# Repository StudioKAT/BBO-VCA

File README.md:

# BBO&VCA

## 概要 / Overview

**BBO&VCA** は、Ieaskul F. Mobenthey の Denum と [crucFX Utility BBO](https://github.com/d42kn355/BoundsBounceOscillator) にインスパイアされた「バウンズ・バウンス・オシレーター（Bounds Bounce Oscillator）」です。  
この回路は、「バウンス（Bounce）」と「バウンズ（Bounds）」という、2つの概念を軸に動作します。  
ボールが2つの壁の間を行き来して跳ねている様子をイメージしてください。バウンスはボールのスピード、バウンズはその2つの壁の距離です。  
このオシレーターでは、バウンスを大きくすると周波数が上がり、バウンズを狭めると振幅が下がる代わりに周波数はさらに上がります。つまり、壁を近づけると、ボール（信号）の移動が速くなるという構造です。  
**BBO&VCA** は、バウンスとバウンズをそれぞれ独立して調整・変調でき、主出力からは常に三角波が出力されます。また、もう1つの出力からは矩形波が得られます。  
さらに、レンジスイッチにより3つの動作範囲を選択できます：
- 標準オーディオレート
- 低オーディオレート
- LFOレート

出力される三角波と矩形波は、それぞれ専用のリニアVCAを通して出力されており、外部CVやノブで音量（振幅）をコントロールできます。  
> ※ 1V/oct の標準CVピッチ制御には対応していません。

**BBO&VCA** is a "Bounds Bounce Oscillator" inspired by Ieaskul F. Mobenthey's *Denum* and the [crucFX Utility BBO](https://github.com/d42kn355/BoundsBounceOscillator).  
This circuit operates based on two key concepts: **Bounce** and **Bounds**.  
Imagine a ball bouncing back and forth between two walls. The **Bounce** represents the speed of the ball, and the **Bounds** represent the distance between the two walls.  

In this oscillator, increasing the Bounce raises the frequency. Narrowing the Bounds further increases the frequency but reduces the amplitude.  
In other words, when the walls are brought closer together, the ball (i.e., the signal) travels faster, resulting in a higher pitch.

**BBO&VCA** allows independent control and modulation of both Bounce and Bounds.  
The main output always produces a triangle wave, while the secondary output provides a square wave.  

A range switch allows you to select from three operating ranges:
- Standard audio rate  
- Low audio rate  
- LFO rate  

Both the triangle and square waves are routed through dedicated linear VCAs, allowing you to control their amplitude (volume) via knobs or external CV.

> *Note: This module does not support standard 1V/oct pitch tracking.*

## 仕様 / Spec
- Format: Eurorack
- Function: Oscillator / LFO
- Current needs: +12V: 30mA, -12V: 30mA
- Width: 8 HP
- Depth: 25mm (including power connector)

## 販売 / Sales

StudioKATオフィシャルショップで販売しています。(日本国内限定)  
 https://www.studiokat.jp/items/113562094

## ライセンス / License

この作品は [Creative Commons 表示 - 継承 4.0 国際 (CC BY-SA 4.0)](https://creativecommons.org/licenses/by-sa/4.0/deed.ja) の下でライセンスされています。  
This work is licensed under the [Creative Commons Attribution-ShareAlike 4.0 International License](https://creativecommons.org/licenses/by-sa/4.0/).

## クレジット / Credits

- Designed by : StudioKAT
- Website : https://www.studiokat.jp/
- GitHub : https://github.com/StudioKAT
- X(Twitter) : https://x.com/StudioKAT_synth
- Instagram : https://www.instagram.com/studiokat_modular/

## 更新履歴 / Changelog

- `2025-07-17` Released version 1.0

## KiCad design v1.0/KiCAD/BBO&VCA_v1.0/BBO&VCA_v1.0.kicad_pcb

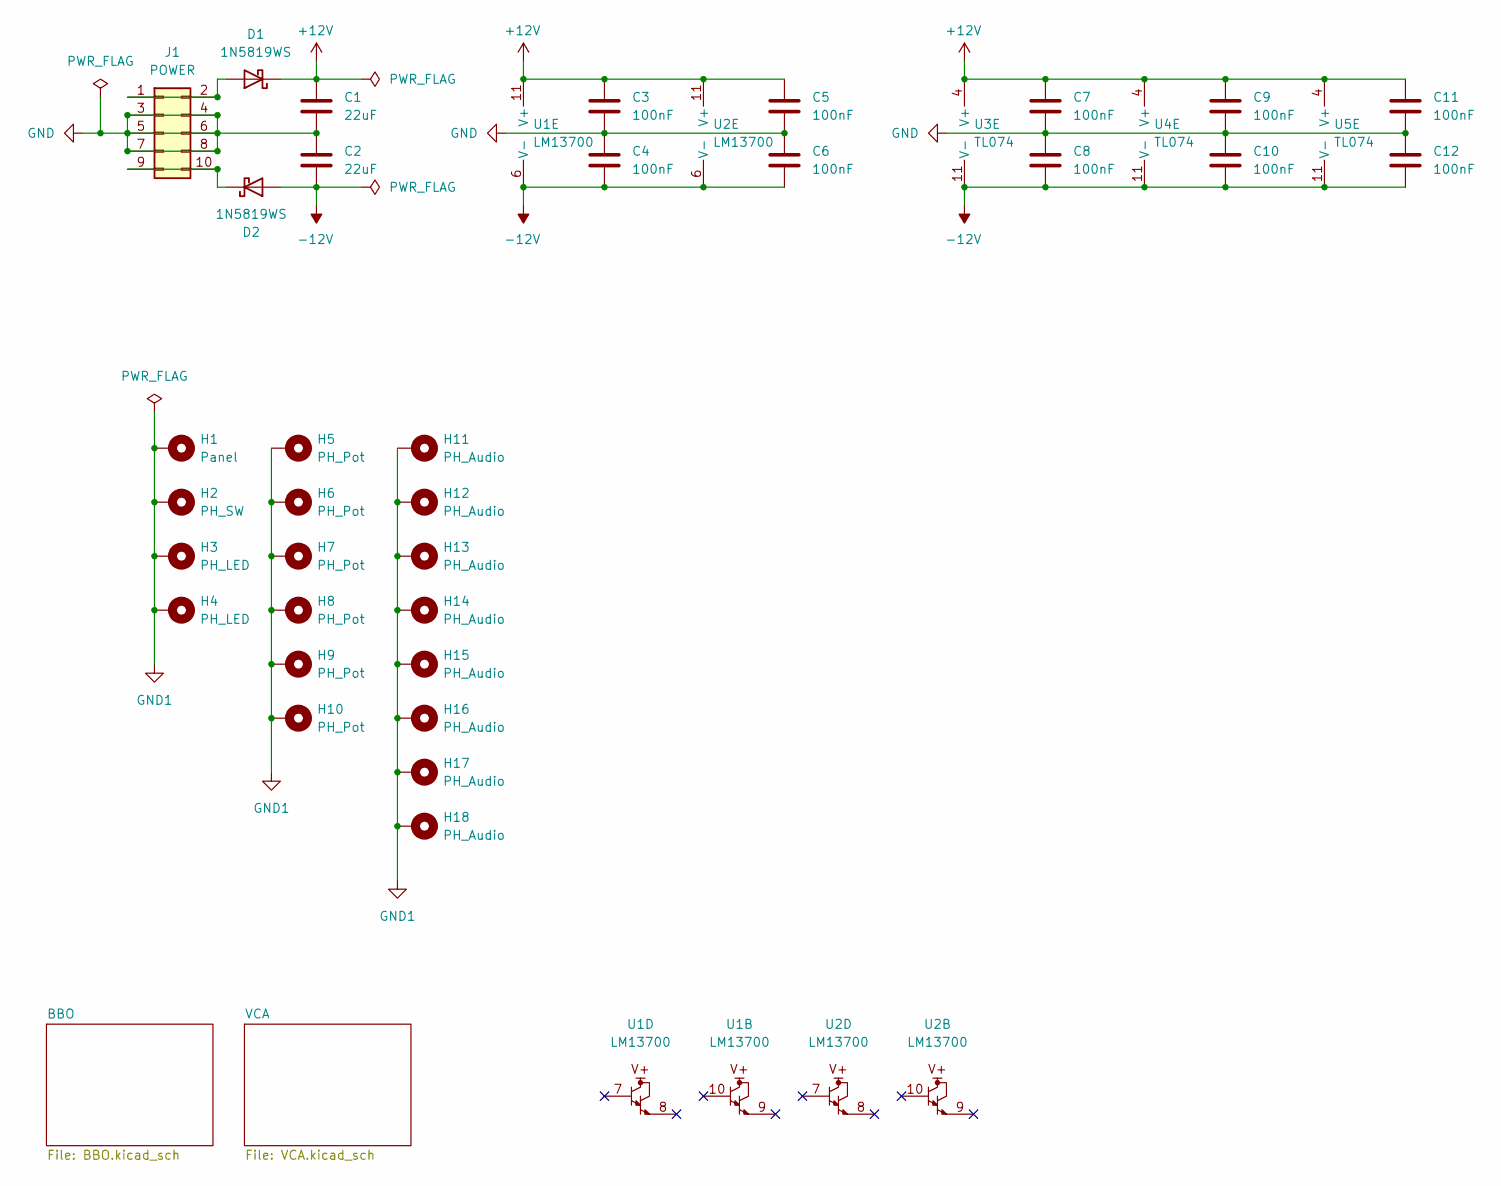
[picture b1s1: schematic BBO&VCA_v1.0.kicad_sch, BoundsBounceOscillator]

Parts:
C1, C2: 22uF; C_0805_2012Metric; LCSC C45783
C3, C4, C5, C6, C7, C8, C9, C10, C11, C12: 100nF; C_0603_1608Metric; LCSC C14663
D1, D2: 1N5819WS; D_SOD-323; LCSC C64886
H1: Panel; Panel_8HP
H2: PH_SW; PH_ToggleSwitch_5.1mm_Pad
H3, H4: PH_LED; PH_LED_3.0mm_Pad
H5, H6, H9, H10: PH_Pot; PH_RK097_15mmKnob_Pad
H7, H8: PH_Pot; PH_RK097_15mmKnob_Uni_Pad
H11, H12, H13, H14, H15, H16, H17, H18: PH_Audio; PH_AudioJack_3.5mm_Pad
J1: POWER; BoxHeader_2x05_2.54mm_Europower_2
U1, U2: LM13700; SOIC-16_3.9x9.9mm_P1.27mm; LCSC C174050
U3, U4, U5: TL074; SOIC-14_3.9x8.7mm_P1.27mm; LCSC C12594

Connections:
+12V: C1.1, C3.1, C5.1, C7.1, C9.1, C11.1, D1.1 (K), U1.11 (V+), U2.11 (V+), U3.4 (V+), U4.4 (V+), U5.4 (V+); also elsewhere on the board
-12V: C2.2, C4.2, C6.2, C8.2, C10.2, C12.2, D2.2 (A), U1.6 (V-), U2.6 (V-), U3.11 (V-), U4.11 (V-), U5.11 (V-); also elsewhere on the board
GND: C1.2, C2.1, C3.2, C4.1, C5.2, C6.1, C7.2, C8.1, C9.2, C10.1, C11.2, C12.1, J1.3, J1.4, J1.5, J1.6, J1.7, J1.8; also elsewhere on the board
GND1: H1.1, H2.1, H3.1, H4.1, H5.1, H6.1, H7.1, H8.1, H9.1, H10.1, H11.1, H12.1, H13.1, H14.1, H15.1, H16.1, H17.1, H18.1
unnamed: D1.2 (A), J1.1, J1.2
unnamed: D2.1 (K), J1.9, J1.10

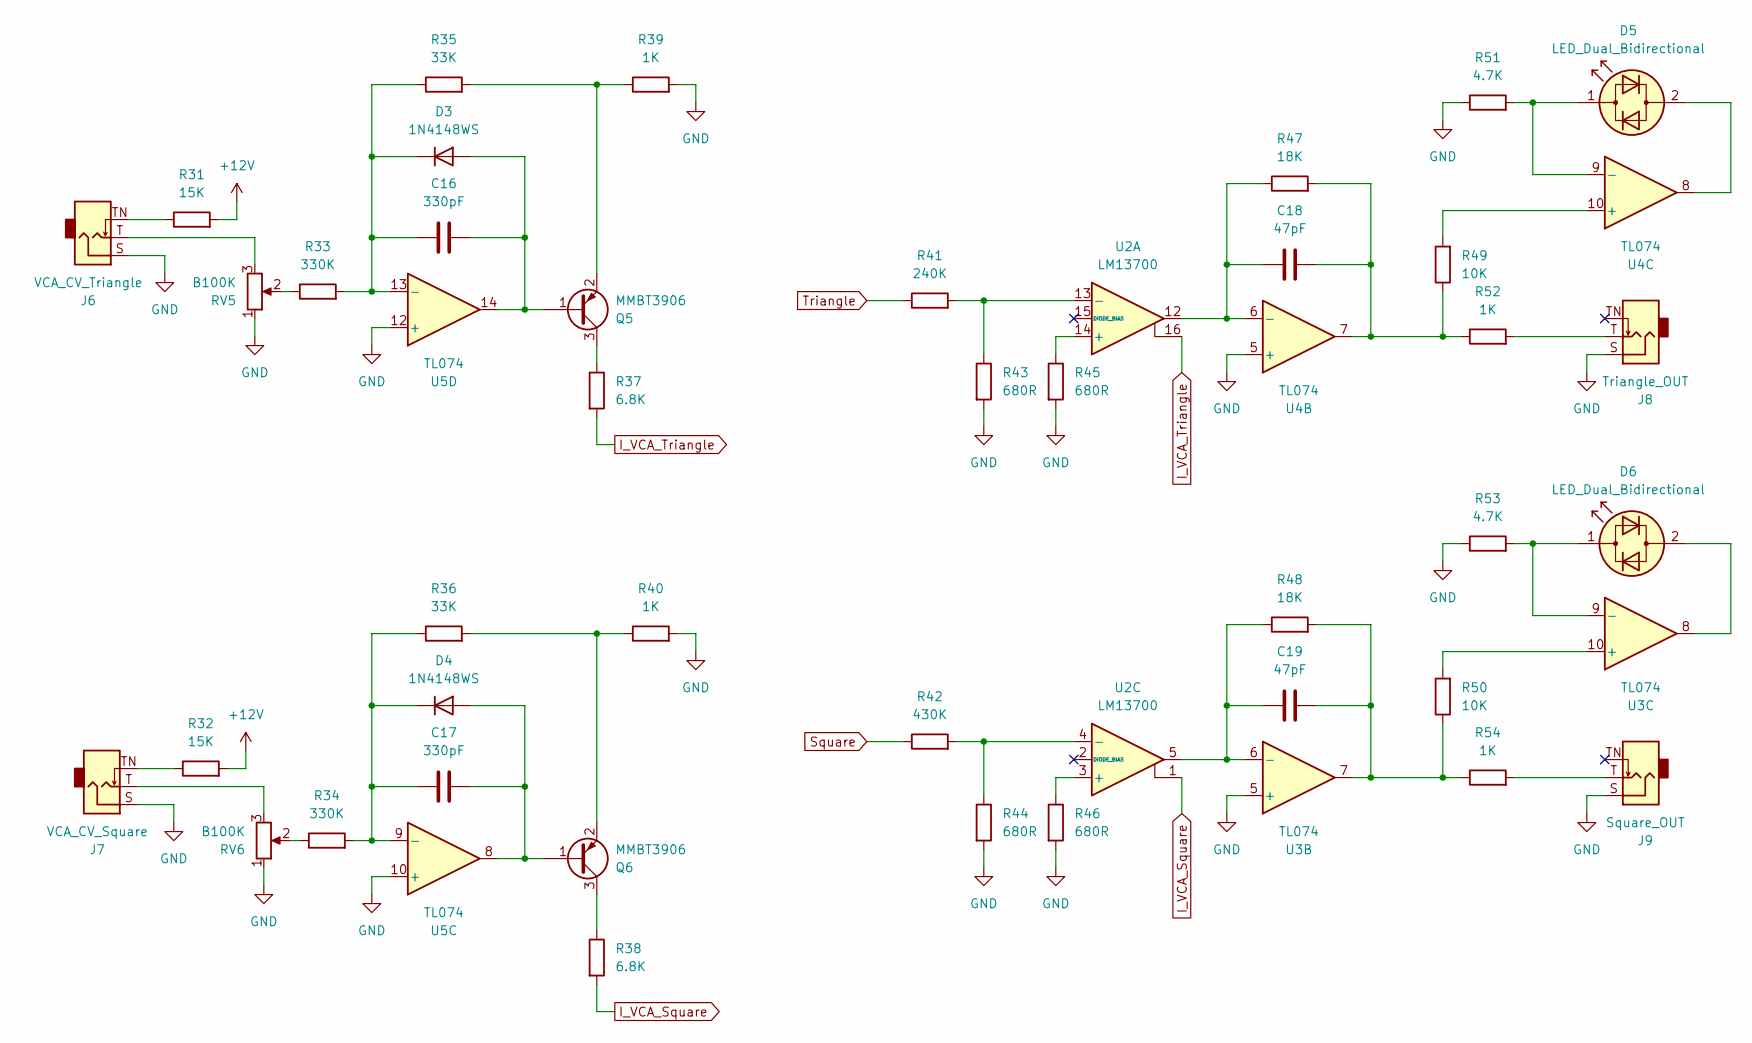
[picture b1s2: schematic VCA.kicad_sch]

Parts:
C16, C17: 330pF; C_0402_1005Metric; LCSC C13533
C18, C19: 47pF; C_0402_1005Metric; LCSC C1567
D3, D4: 1N4148WS; D_SOD-323; LCSC C2128
D5, D6: LED_Dual_Bidirectional; LED_D3.0mm
J6: VCA_CV_Triangle; AudioJack_PJ301M-12
J7: VCA_CV_Square; AudioJack_PJ301M-12
J8: Triangle_OUT; AudioJack_PJ301M-12
J9: Square_OUT; AudioJack_PJ301M-12
Q5, Q6: MMBT3906; SOT-23; LCSC C7420354
R31, R32: 15K; R_0603_1608Metric; LCSC C22809
R33, R34: 330K; R_0402_1005Metric; LCSC C25778
R35, R36: 33K; R_0402_1005Metric; LCSC C25779
R37, R38: 6.8K; R_0402_1005Metric; LCSC C25917
R39, R40, R52, R54: 1K; R_0402_1005Metric; LCSC C11702
R41: 240K; R_0603_1608Metric; LCSC C4197
R42: 430K; R_0603_1608Metric; LCSC C25969
R43, R44, R45, R46: 680R; R_0402_1005Metric; LCSC C25130
R47, R48: 18K; R_0402_1005Metric; LCSC C25762
R49, R50: 10K; R_0402_1005Metric; LCSC C25744
R51, R53: 4.7K; R_0402_1005Metric; LCSC C25900
RV5, RV6: B100K; Potentiometer_RV09
U2: LM13700; SOIC-16_3.9x9.9mm_P1.27mm; LCSC C174050
U3, U4, U5: TL074; SOIC-14_3.9x8.7mm_P1.27mm; LCSC C12594

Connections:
+12V: R31.2, R32.2; also elsewhere on the board
GND: J6.S, J7.S, J8.S, J9.S, R39.2, R40.2, R43.2, R44.2, R45.2, R46.2, R51.1, R53.1, RV5.1, RV6.1, U3.5 (+), U4.5 (+), U5.10 (+), U5.12 (+); also elsewhere on the board
I_VCA_Square: R38.2, U2.1
I_VCA_Triangle: R37.2, U2.16
unnamed: C18.2, R47.2, R49.1, R52.1, U4.7
unnamed: C19.2, R48.2, R50.1, R54.1, U3.7
unnamed: C16.2, D3.2 (A), Q5.1 (B), U5.14
unnamed: C16.1, D3.1 (K), R33.2, R35.1, U5.13 (-)
unnamed: C17.2, D4.2 (A), Q6.1 (B), U5.8
unnamed: C17.1, D4.1 (K), R34.2, R36.1, U5.9 (-)
unnamed: D5.2 (AK), U4.8
unnamed: D5.1 (KA), R51.2, U4.9 (-)
unnamed: D6.2 (AK), U3.8
unnamed: D6.1 (KA), R53.2, U3.9 (-)
unnamed: J6.T, RV5.3
unnamed: J6.TN, R31.1
unnamed: J7.T, RV6.3
unnamed: J7.TN, R32.1
unnamed: J8.T, R52.2
unnamed: J9.T, R54.2
unnamed: Q5.3 (C), R37.1
unnamed: Q5.2 (E), R35.2, R39.1
unnamed: Q6.3 (C), R38.1
unnamed: Q6.2 (E), R36.2, R40.1
unnamed: R33.1, RV5.2
unnamed: R34.1, RV6.2
unnamed: R45.1, U2.14 (+)
unnamed: R41.2, R43.1, U2.13 (-)
unnamed: R46.1, U2.3 (+)
unnamed: R42.2, R44.1, U2.4 (-)
unnamed: C19.1, R48.1, U2.5, U3.6 (-)
unnamed: R50.2, U3.10 (+)
unnamed: C18.1, R47.1, U2.12, U4.6 (-)
unnamed: R49.2, U4.10 (+)
Square: R42.1; also elsewhere on the board
Triangle: R41.1; also elsewhere on the board

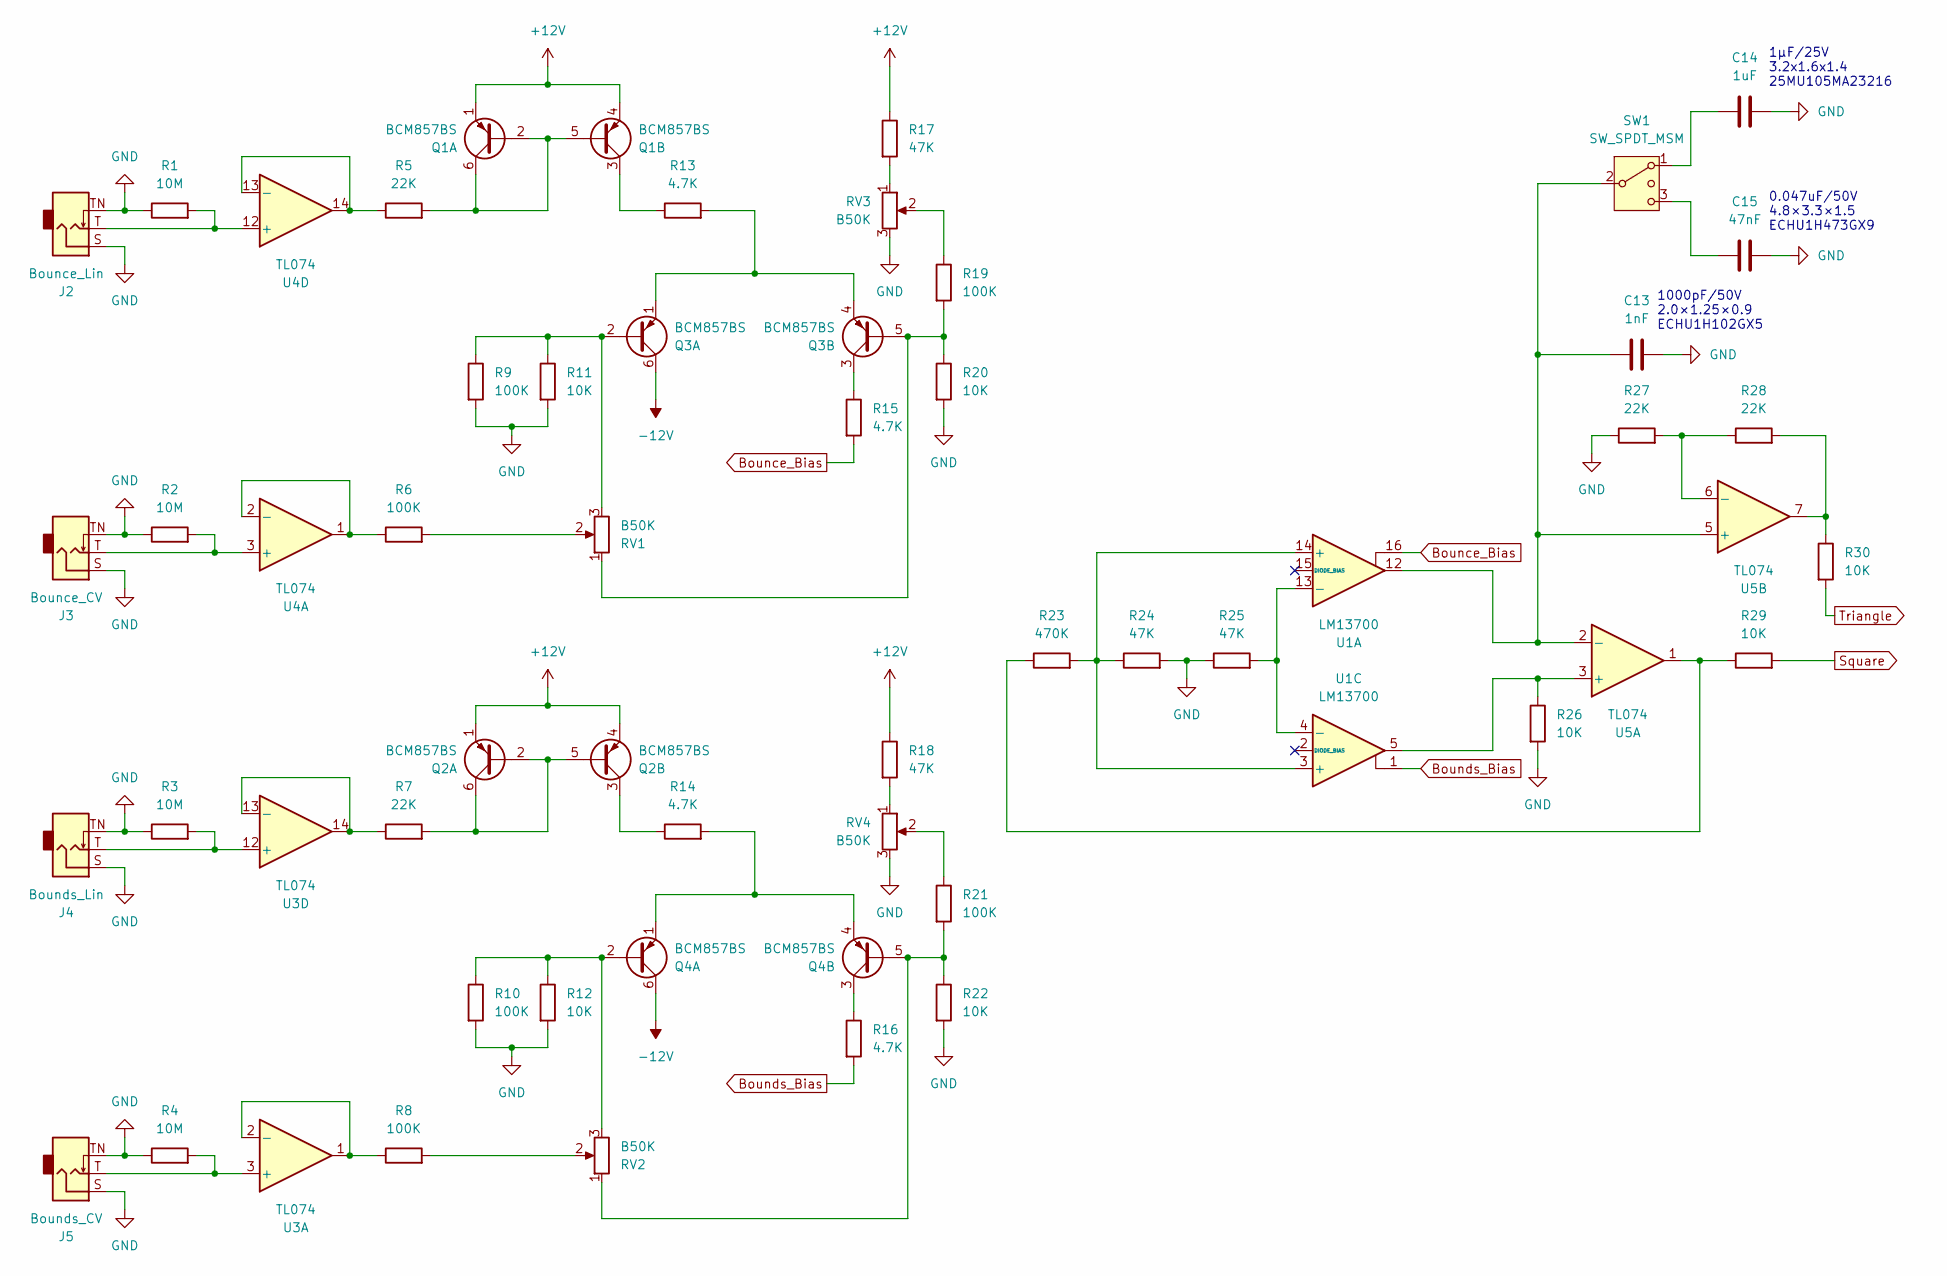
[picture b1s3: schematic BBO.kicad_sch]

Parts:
C13: 1nF; C_0805_2012Metric_Pad1.18x1.45mm_HandSolder
C14: 1uF; C_1206_3216Metric_Pad1.33x1.80mm_HandSolder
C15: 47nF; C_1913_4833Metric
J2: Bounce_Lin; AudioJack_PJ301M-12
J3: Bounce_CV; AudioJack_PJ301M-12
J4: Bounds_Lin; AudioJack_PJ301M-12
J5: Bounds_CV; AudioJack_PJ301M-12
Q1, Q2, Q3, Q4: BCM857BS; SOT-363_SC-70-6; LCSC C20426291
R1, R2, R3, R4: 10M; R_0402_1005Metric; LCSC C26082
R5, R7, R27, R28: 22K; R_0402_1005Metric; LCSC C25768
R6, R8, R9, R10, R19, R21: 100K; R_0402_1005Metric; LCSC C25741
R11, R12, R20, R22, R26, R29, R30: 10K; R_0402_1005Metric; LCSC C25744
R13, R14, R15, R16: 4.7K; R_0402_1005Metric; LCSC C25900
R17, R18, R24, R25: 47K; R_0402_1005Metric; LCSC C25792
R23: 470K; R_0402_1005Metric; LCSC C25790
RV1, RV2, RV3, RV4: B50K; Potentiometer_RV09
SW1: SW_SPDT_MSM; ToggleSwitch_2MS1-T2-B4-M2-Q-E-S
U1: LM13700; SOIC-16_3.9x9.9mm_P1.27mm; LCSC C174050
U3, U4, U5: TL074; SOIC-14_3.9x8.7mm_P1.27mm; LCSC C12594

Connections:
+12V: Q1.1 (E1), Q1.4 (E2), Q2.1 (E1), Q2.4 (E2), R17.1, R18.1; also elsewhere on the board
-12V: Q3.6 (C1), Q4.6 (C1); also elsewhere on the board
Bounce_Bias: R15.2, U1.16
Bounds_Bias: R16.2, U1.1
GND: C13.2, C14.2, C15.2, J2.S, J2.TN, J3.S, J3.TN, J4.S, J4.TN, J5.S, J5.TN, R1.1, R2.1, R3.1, R4.1, R9.2, R10.2, R11.2, R12.2, R20.2, R22.2, R24.2, R25.1, R26.2, R27.1, RV3.3, RV4.3; also elsewhere on the board
unnamed: C14.1, SW1.1
unnamed: Q1.2 (B1), Q1.5 (B2), Q1.6 (C1), R5.2
unnamed: Q1.3 (C2), R13.1
unnamed: Q2.2 (B1), Q2.5 (B2), Q2.6 (C1), R7.2
unnamed: Q2.3 (C2), R14.1
unnamed: Q3.2 (B1), R9.1, R11.1, RV1.3
unnamed: Q3.1 (E1), Q3.4 (E2), R13.2
unnamed: Q3.5 (B2), R19.2, R20.1, RV1.1
unnamed: Q3.3 (C2), R15.1
unnamed: Q4.2 (B1), R10.1, R12.1, RV2.3
unnamed: Q4.1 (E1), Q4.4 (E2), R14.2
unnamed: Q4.5 (B2), R21.2, R22.1, RV2.1
unnamed: Q4.3 (C2), R16.1
unnamed: R6.2, RV1.2
unnamed: R8.2, RV2.2
unnamed: R17.2, RV3.1
unnamed: R18.2, RV4.1
unnamed: R19.1, RV3.2
unnamed: R21.1, RV4.2
unnamed: R23.1, R29.1, U5.1
unnamed: R28.2, R30.1, U5.7
unnamed: C13.1, SW1.2 (3), U1.12, U5.2 (-), U5.5 (+)
unnamed: C15.1, SW1.3 (4)
unnamed: R23.2, R24.1, U1.3 (+), U1.14 (+)
unnamed: R25.2, U1.4 (-), U1.13 (-)
unnamed: J5.T, R4.2, U3.3 (+)
unnamed: R8.1, U3.1, U3.2 (-)
unnamed: J4.T, R3.2, U3.12 (+)
unnamed: R7.1, U3.13 (-), U3.14
unnamed: J3.T, R2.2, U4.3 (+)
unnamed: R6.1, U4.1, U4.2 (-)
unnamed: J2.T, R1.2, U4.12 (+)
unnamed: R5.1, U4.13 (-), U4.14
unnamed: R26.1, U1.5, U5.3 (+)
unnamed: R27.2, R28.1, U5.6 (-)
Square: R29.2; also elsewhere on the board
Triangle: R30.2; also elsewhere on the board

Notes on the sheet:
0.047uF/50V 4.8×3.3×1.5 ECHU1H473GX9
1μF/25V 3.2x1.6x1.4 25MU105MA23216
1000pF/50V 2.0×1.25×0.9 ECHU1H102GX5

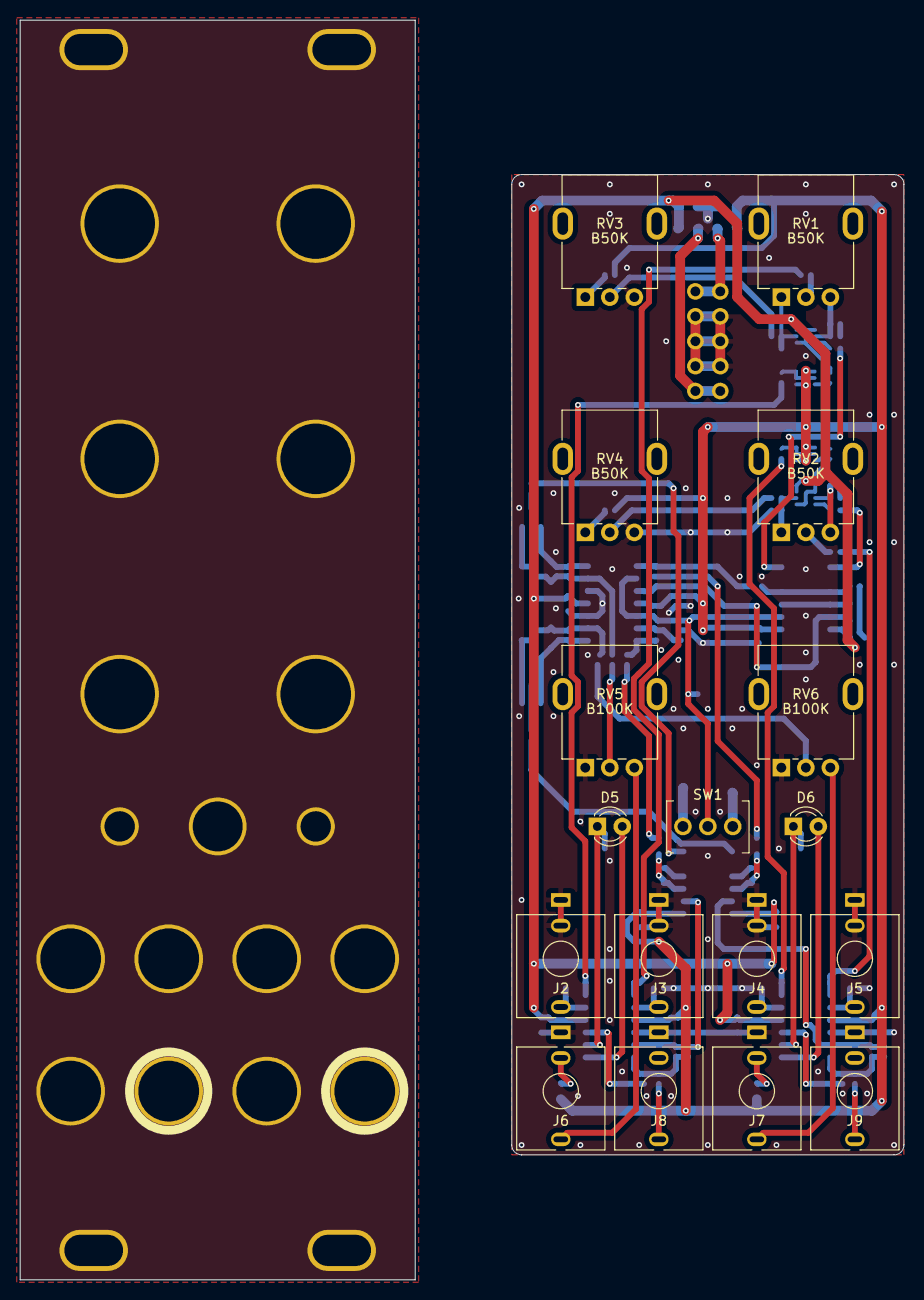
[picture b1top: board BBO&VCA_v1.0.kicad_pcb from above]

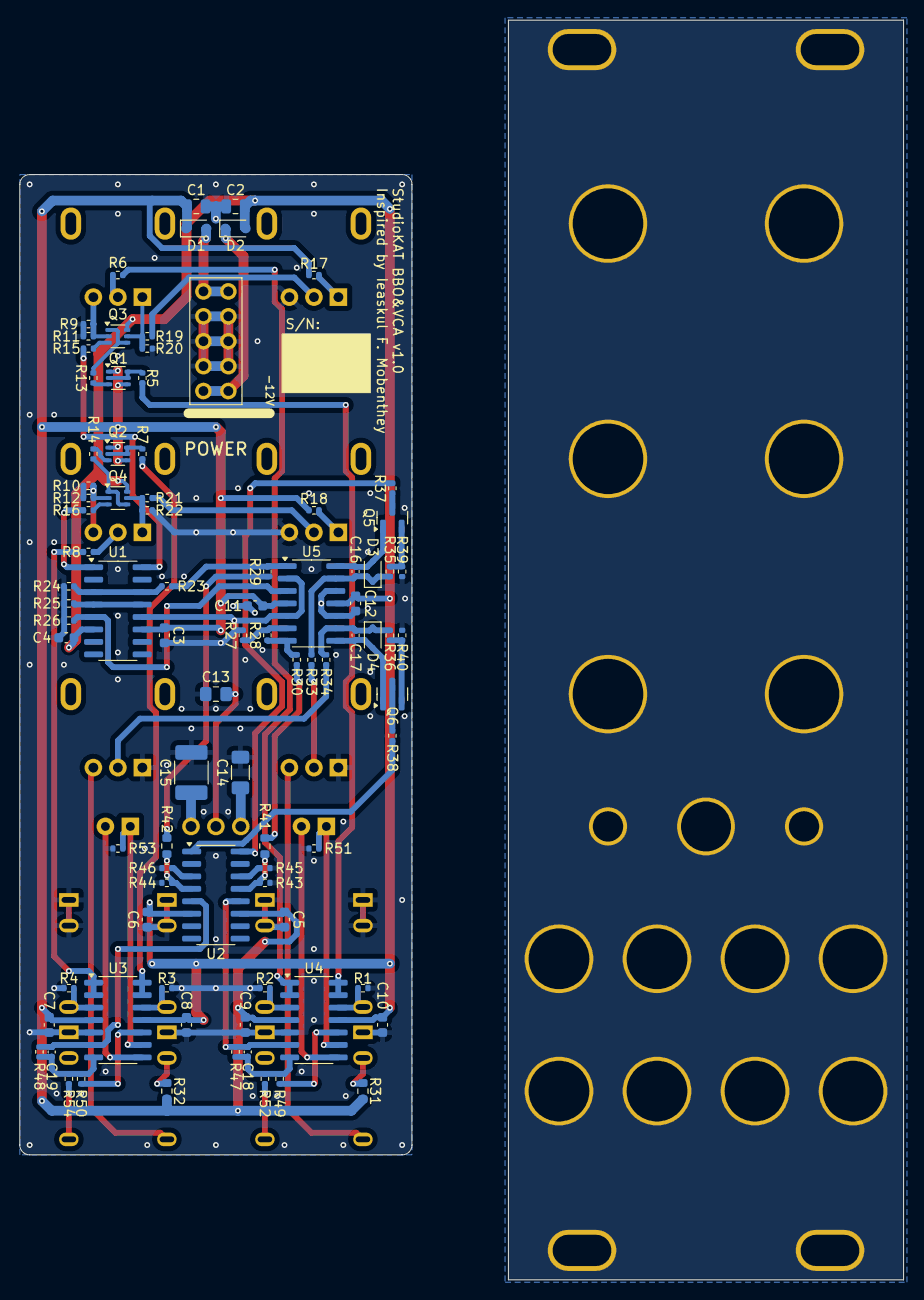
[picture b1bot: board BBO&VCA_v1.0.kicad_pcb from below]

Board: 2 copper layers, 90.1 x 128.5 mm, 124 parts (89 on the bottom side), 77 nets.

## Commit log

2025-07-16 販売ページURL追加
2025-07-19 消費電力を実測値に変更
